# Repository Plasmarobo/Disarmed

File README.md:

# DISARMED!

Heavily inspired by [Keep Talking and Nobody Explodes](https://keeptalkinggame.com/) and [Bomb Corp](https://www.jackboxgames.com/bomb-corp/).

A physical "Bop-It for adults". 

This ammounts to a electroncs and software programming project, with a side-helping of game design and art!

## The SSD Control Panel
The SSD Control panel provides control lines (including manually adjustable brightness) for up to 8 SSD panels with 4 digits each. That is a grand total of 32 digits per board, with 4 brightness zones.
This board is driven by an ATTiny85, which provide an I2C interface to the system at large, and shifts out data to the LED driver chips.
Software will come later.

## The Analog Control Panel
The analog control panel uses DAC and ADC chips to provide analog read and write functions. External I2C interface provided by an ATTiny85. 
The software drivers for this board are still in the works. It will eventually be able to read from analog inputs and write to some interesting analog displays!

## The Switch Control Board
The Switch Control Board uses a number of digital I/O expanders to provide a vast number of pulled-up digital inputs. It has an ATMega328 on board. The Mega chip, with more ports and power, gives us and on-board USB port for programming and diagnostics. The many serial peripherals juggle the master relationship with the expanders and the slave relationship with the external system. Some pins are enabled to drive optional LEDs connected to the switches or mounted on the display.

The software for this is not yet written, but I'm looking forward to the increased power and peripherals vs the ATTiny85.

### The Switch Board
The switch panel contains both analog potentiometers and SPST switches. These will be the primary user input at some point.
Shown is an early prototype of the layout. Eventually more complex and varied inputs will be added. Some of the empty cutouts are for SSD displays not pictured.

The eventual plan is to laser cut and paint and acrylic panel to fit into a case. An alternative may be to 3D print some slotable modules and a motherboard panel to hold them.

## The LED Module
The LED Module drives a series of LED Bar Graph displays, including a few unique circular displays.
The board is essentially a giant shift register that can source proper current to each LED.

Lesson Learned: Double, Triple, Quadruple check your sizing on parts. I eneded up using an ultra-fine pitch SMD resistor array.
I managed to get a few of them down successfully, but ended up bridging the others. My solution was to cut the traces and manually solder THT resistors on the back of the panel.
Fixed in the other designs: used much larger chip resistors.

The board is driven by an onboard ATTiny85, running some custom firmware that includes the TinyWireS library. Unfortunately still interating on the software, but the chip provides and I2C slave that allows a master to write to an output array: buffering the shift register output.
The same set of pins is also used as the ISP interface.

A NodeMCU ESP8266 breakout is being used as a i2c master test.

## The SSD Module
The Seven Segment Display Module is something I unfortunately based on the LD8041C/D series of 20mm seven segment displays.
Having bought several 10 years ago, I found that they seem to be no longer manufactured, so I just have the one board that is finished.
JCLPCB manufactures in minimum lots of 5, so I have 4 useless, large PCBs. At least the one works.

(For the REV2 board, the one I got manufactured, I accidently left out a single line segment of a trace when refactoring some of the runs... thankfully, I was able to bridge the gap with a single wire. This is fixed in REV3+).

In the future, I'll source some new SSD parts and update the boards, possibly with a denser layout.

The board uses MAX7219CNG LED/IO drivers over SPI. A MCP41010 is used to digitally control ISET, though in practice this was set to it's maximum value, and the SSD brightness is controlled via the Intensity register rin the MAX7219.

The test code was prototyped on a NodeMCU ESP8266 breakout, and then ported down to a Adafruit Trinket (ATTiny85). The TinySPI library was used to bridge the gaps.

I tried using libraries for both the MAX7219 and MCP41010 chip, but took exception to the complexity of the code and ended up implementing my own simple driving functions.
Future revisions of the board may implement an I2C interface and use an on-board MCU to drive the MAC7219 and MCP41010.

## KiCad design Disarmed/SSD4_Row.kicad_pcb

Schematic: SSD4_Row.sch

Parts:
D1, D2, D3, D4: HDSP-5500; VDMRX10C0
J1: Conn_02x02_Odd_Even; PinSocket_2x02_P2.54mm_Vertical
J2: Conn_02x04_Odd_Even; PinSocket_2x04_P2.54mm_Vertical

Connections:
/DIG_0: D1.3 (COM), D1.8 (COM), J1.1
/DIG_1: D2.3 (COM), D2.8 (COM), J1.3
/DIG_2: D3.3 (COM), D3.8 (COM), J1.2
/DIG_3: D4.3 (COM), D4.8 (COM), J1.4
/SEG_A: D1.7 (A), D2.7 (A), D3.7 (A), D4.7 (A), J2.7
/SEG_B: D1.6 (B), D2.6 (B), D3.6 (B), D4.6 (B), J2.5
/SEG_C: D1.4 (C), D2.4 (C), D3.4 (C), D4.4 (C), J2.6
/SEG_D: D1.2 (D), D2.2 (D), D3.2 (D), D4.2 (D), J2.4
/SEG_DP: D1.5 (DP), D2.5 (DP), D3.5 (DP), D4.5 (DP), J2.8
/SEG_E: D1.1 (E), D2.1 (E), D3.1 (E), D4.1 (E), J2.2
/SEG_F: D1.9 (F), D2.9 (F), D3.9 (F), D4.9 (F), J2.1
/SEG_G: D1.10 (G), D2.10 (G), D3.10 (G), D4.10 (G), J2.3

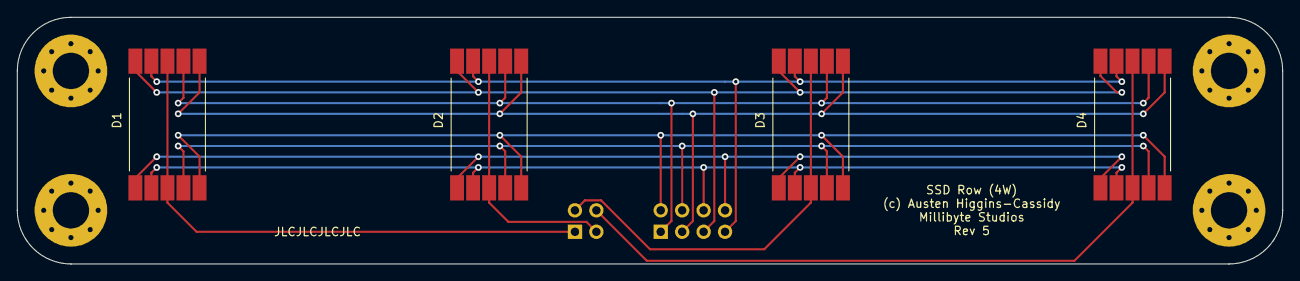
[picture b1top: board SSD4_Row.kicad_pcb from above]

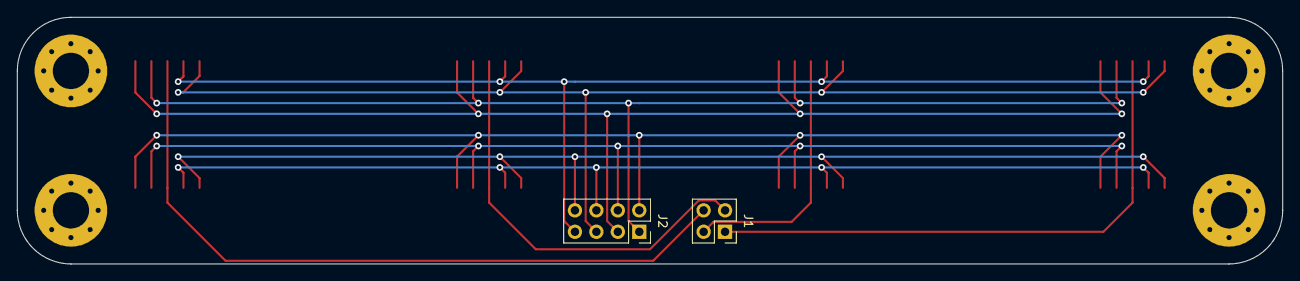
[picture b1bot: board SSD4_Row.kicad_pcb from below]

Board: 2 copper layers, 149.9 x 29.2 mm, 6 parts (2 on the bottom side), 12 nets.

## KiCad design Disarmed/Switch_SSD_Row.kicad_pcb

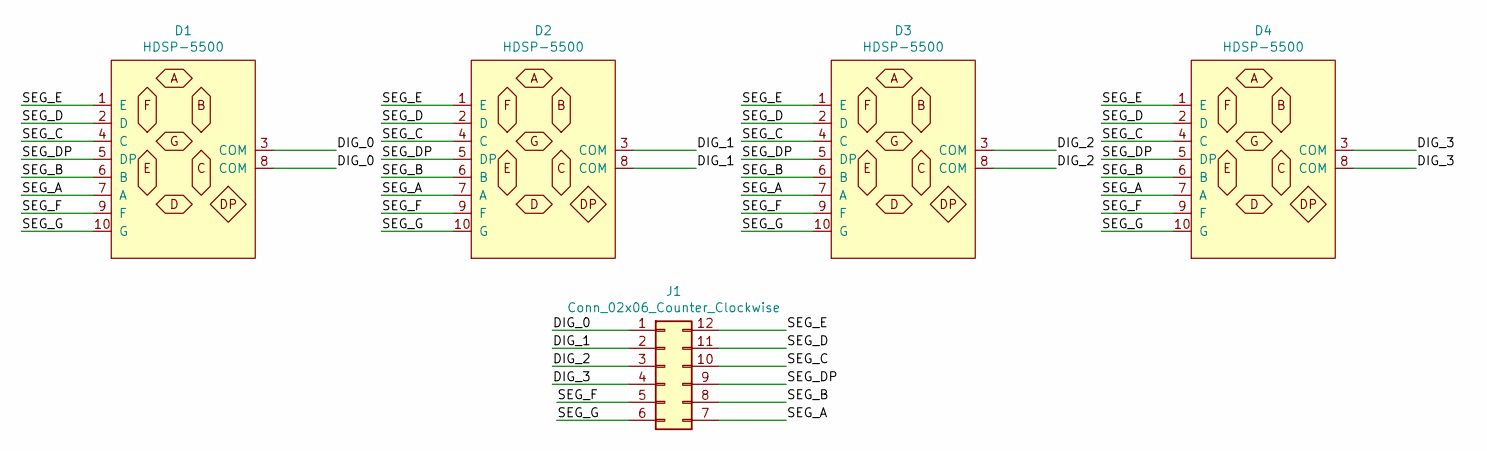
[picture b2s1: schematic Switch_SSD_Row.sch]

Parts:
D1, D2, D3, D4: HDSP-5500
J1: Conn_02x06_Counter_Clockwise; PinSocket_2x06_P2.54mm_Vertical

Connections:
/DIG_0: D1.3 (COM), D1.8 (COM), J1.1
/DIG_1: D2.3 (COM), D2.8 (COM), J1.2
/DIG_2: D3.3 (COM), D3.8 (COM), J1.3
/DIG_3: D4.3 (COM), D4.8 (COM), J1.4
/SEG_A: D1.7 (A), D2.7 (A), D3.7 (A), D4.7 (A), J1.7
/SEG_B: D1.6 (B), D2.6 (B), D3.6 (B), D4.6 (B), J1.8
/SEG_C: D1.4 (C), D2.4 (C), D3.4 (C), D4.4 (C), J1.10
/SEG_D: D1.2 (D), D2.2 (D), D3.2 (D), D4.2 (D), J1.11
/SEG_DP: D1.5 (DP), D2.5 (DP), D3.5 (DP), D4.5 (DP), J1.9
/SEG_E: D1.1 (E), D2.1 (E), D3.1 (E), D4.1 (E), J1.12
/SEG_F: D1.9 (F), D2.9 (F), D3.9 (F), D4.9 (F), J1.5
/SEG_G: D1.10 (G), D2.10 (G), D3.10 (G), D4.10 (G), J1.6

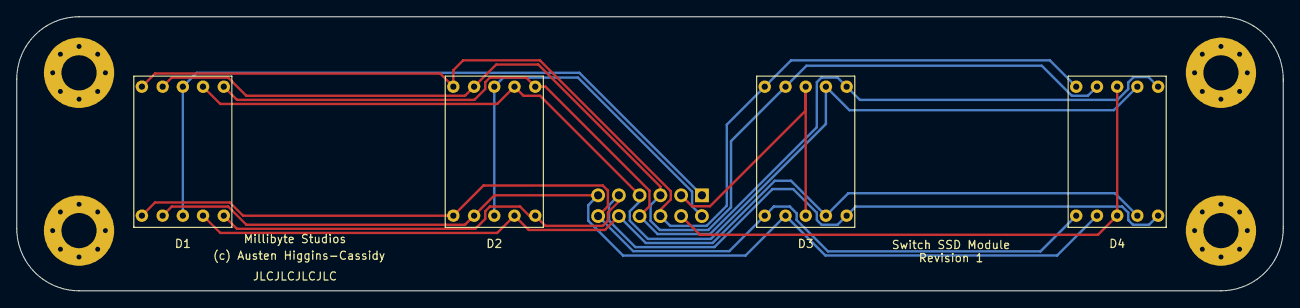
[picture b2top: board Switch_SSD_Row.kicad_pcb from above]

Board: 2 copper layers, 154.9 x 33.5 mm, 5 parts (1 on the bottom side), 12 nets.

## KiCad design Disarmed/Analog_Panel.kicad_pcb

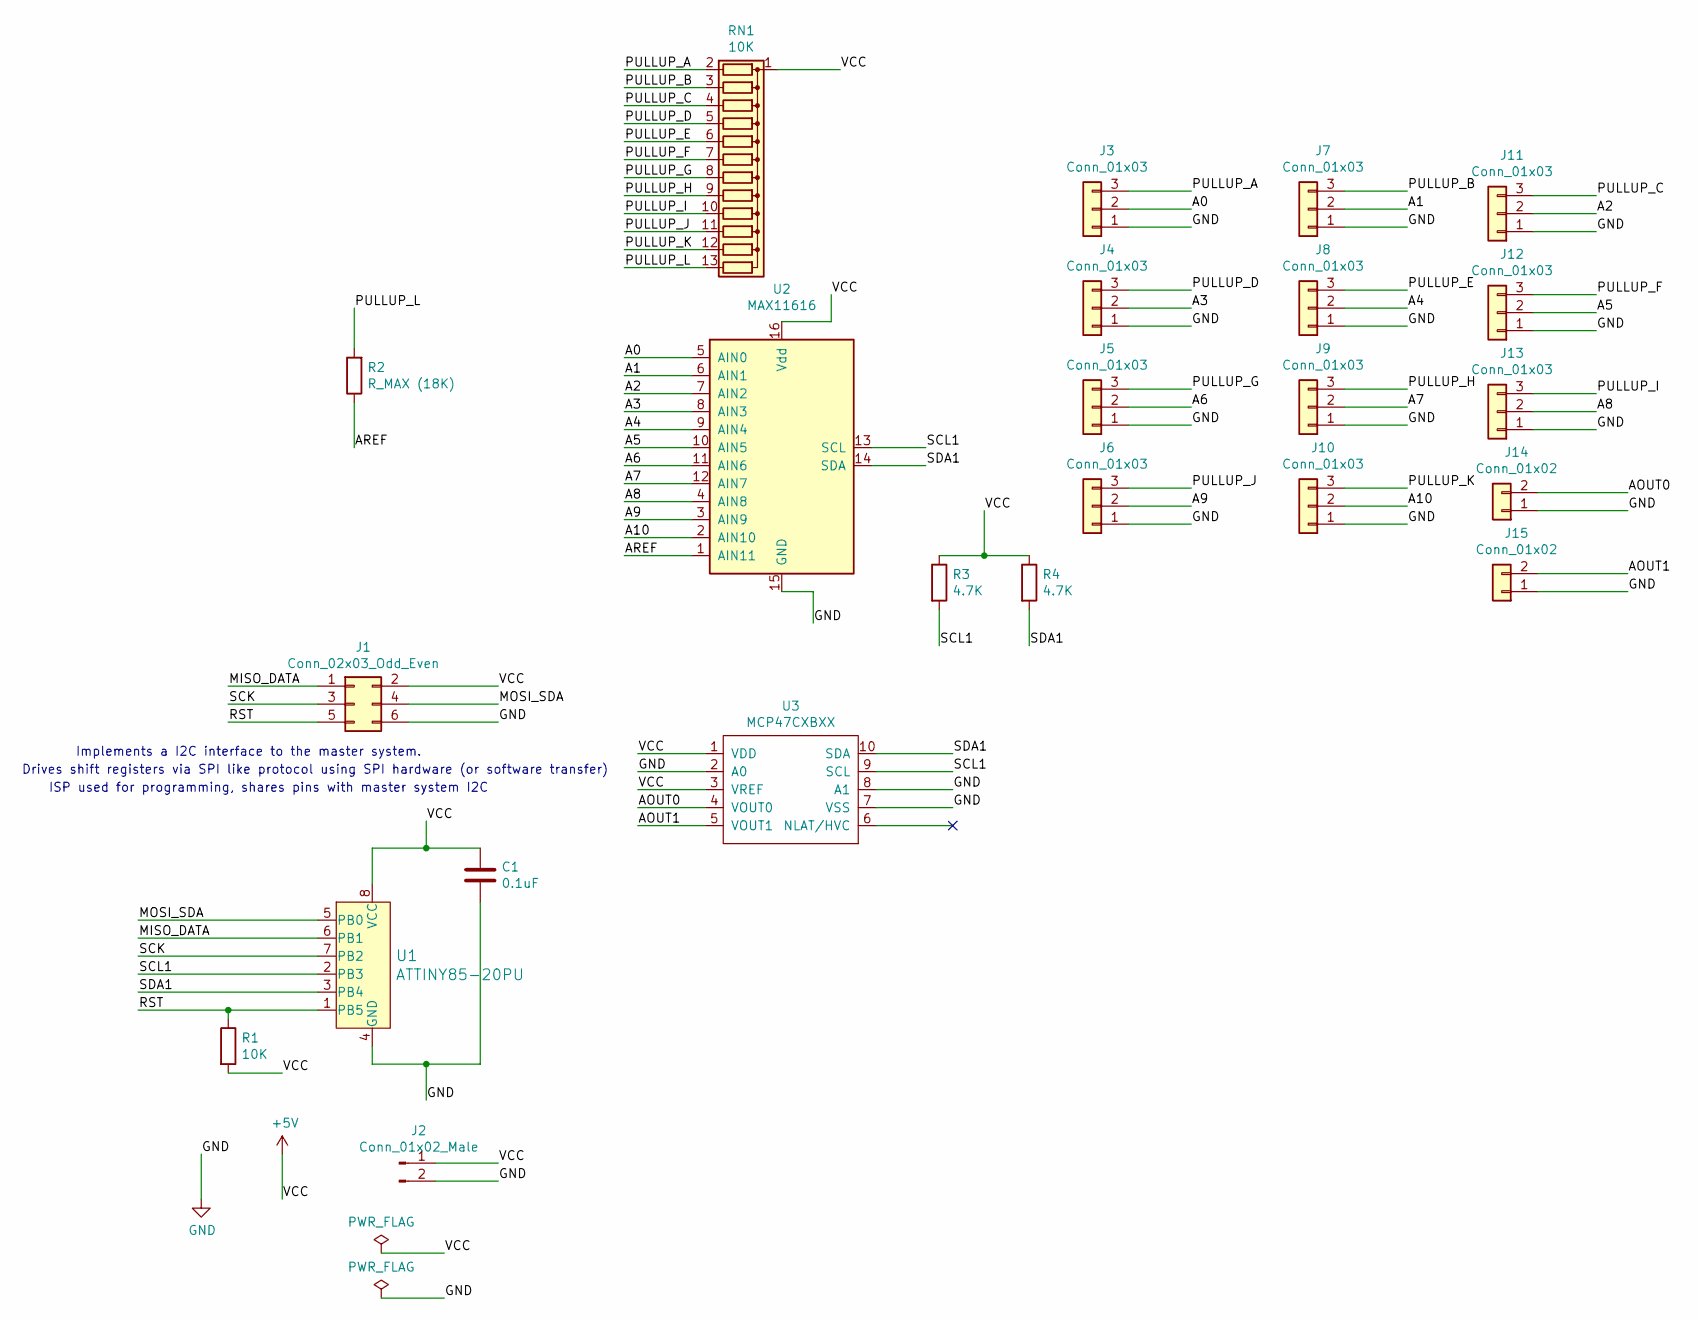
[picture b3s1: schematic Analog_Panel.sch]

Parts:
C1: 0.1uF; C_1812_4532Metric_Pad1.57x3.40mm_HandSolder
J1: Conn_02x03_Odd_Even; PinHeader_2x03_P2.54mm_Vertical
J2: Conn_01x02_Male; PinHeader_1x02_P2.54mm_Vertical
J3, J4, J5, J6, J7, J8, J9, J10, J11, J12, J13: Conn_01x03; PinSocket_1x03_P2.54mm_Vertical
J14, J15: Conn_01x02; PinSocket_1x02_P2.54mm_Vertical
R1: 10K; R_1210_3225Metric_Pad1.30x2.65mm_HandSolder
R2: R_MAX (18K); R_1210_3225Metric_Pad1.30x2.65mm_HandSolder
R3, R4: 4.7K; R_1210_3225Metric_Pad1.30x2.65mm_HandSolder
RN1: 10K; 4814P-2-103LF
U1: ATTINY85-20PU; DIP-8_W7.62mm; MPN ATTINY85-20PU; Digi-Key_PN ATTINY85-20PU-ND
U2: MAX11616; QSOP-16_3.9x4.9mm_P0.635mm
U3: MCP47CXBXX; MSOP-10-1EP_3x3mm_P0.5mm_EP1.68x1.88mm_ThermalVias

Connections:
+5V: C1.1, J1.2, J2.1, R1.2, R3.1, R4.1, RN1.1 (common), U1.8 (VCC), U2.16 (Vdd), U3.1 (VDD), U3.3 (VREF)
/A0: J3.2, U2.5 (AIN0)
/A1: J7.2, U2.6 (AIN1)
/A2: J11.2, U2.7 (AIN2)
/A3: J4.2, U2.8 (AIN3)
/A4: J8.2, U2.9 (AIN4)
/A5: J12.2, U2.10 (AIN5)
/A6: J5.2, U2.11 (AIN6)
/A7: J9.2, U2.12 (AIN7)
/A8: J13.2, U2.4 (AIN8)
/A9: J6.2, U2.3 (AIN9)
/A10: J10.2, U2.2 (AIN10)
/AOUT0: J14.2, U3.4 (VOUT0)
/AOUT1: J15.2, U3.5 (VOUT1)
/AREF: R2.1, U2.1 (AIN11)
/MISO_DATA: J1.1, U1.6 (PB1)
/MOSI_SDA: J1.4, U1.5 (PB0)
/PULLUP_A: J3.3, RN1.2 (R1)
/PULLUP_B: J7.3, RN1.3 (R2)
/PULLUP_C: J11.3, RN1.4 (R3)
/PULLUP_D: J4.3, RN1.5 (R4)
/PULLUP_E: J8.3, RN1.6 (R5)
/PULLUP_F: J12.3, RN1.7 (R6)
/PULLUP_G: J5.3, RN1.8 (R7)
/PULLUP_H: J9.3, RN1.9 (R8)
/PULLUP_I: J13.3, RN1.10 (R9)
/PULLUP_J: J6.3, RN1.11 (R10)
/PULLUP_K: J10.3, RN1.12 (R11)
/PULLUP_L: R2.2, RN1.13 (R12)
/RST: J1.5, R1.1, U1.1 (PB5)
/SCK: J1.3, U1.7 (PB2)
/SCL1: R3.2, U1.2 (PB3), U2.13 (SCL), U3.9 (SCL)
/SDA1: R4.2, U1.3 (PB4), U2.14 (SDA), U3.10 (SDA)
GND: C1.2, J1.6, J2.2, J3.1, J4.1, J5.1, J6.1, J7.1, J8.1, J9.1, J10.1, J11.1, J12.1, J13.1, J14.1, J15.1, U1.4 (GND), U2.15 (GND), U3.2 (A0), U3.7 (VSS), U3.8 (A1)

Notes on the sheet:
Implements a I2C interface to the master system.
Drives shift registers via SPI like protocol using SPI hardware (or software transfer)
ISP used for programming, shares pins with master system I2C

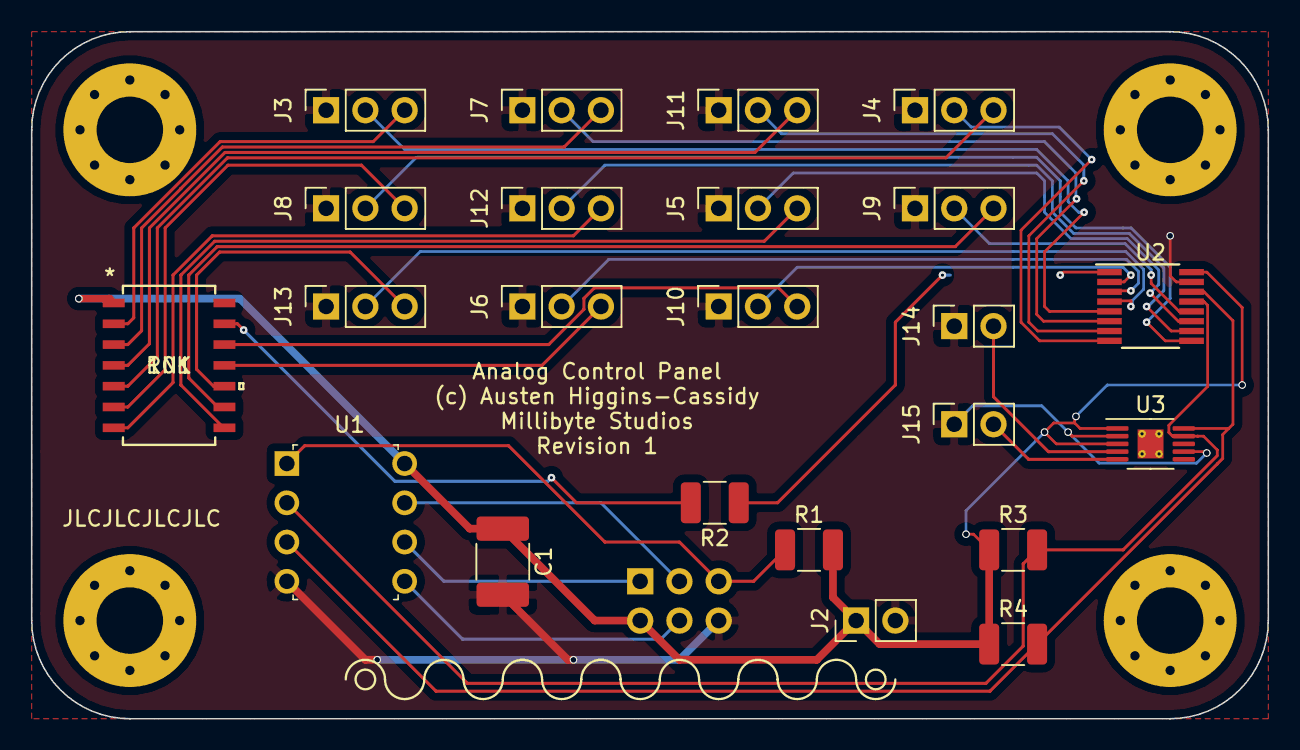
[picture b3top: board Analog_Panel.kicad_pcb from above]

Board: 2 copper layers, 80.0 x 44.5 mm, 24 parts (1 on the bottom side), 34 nets.

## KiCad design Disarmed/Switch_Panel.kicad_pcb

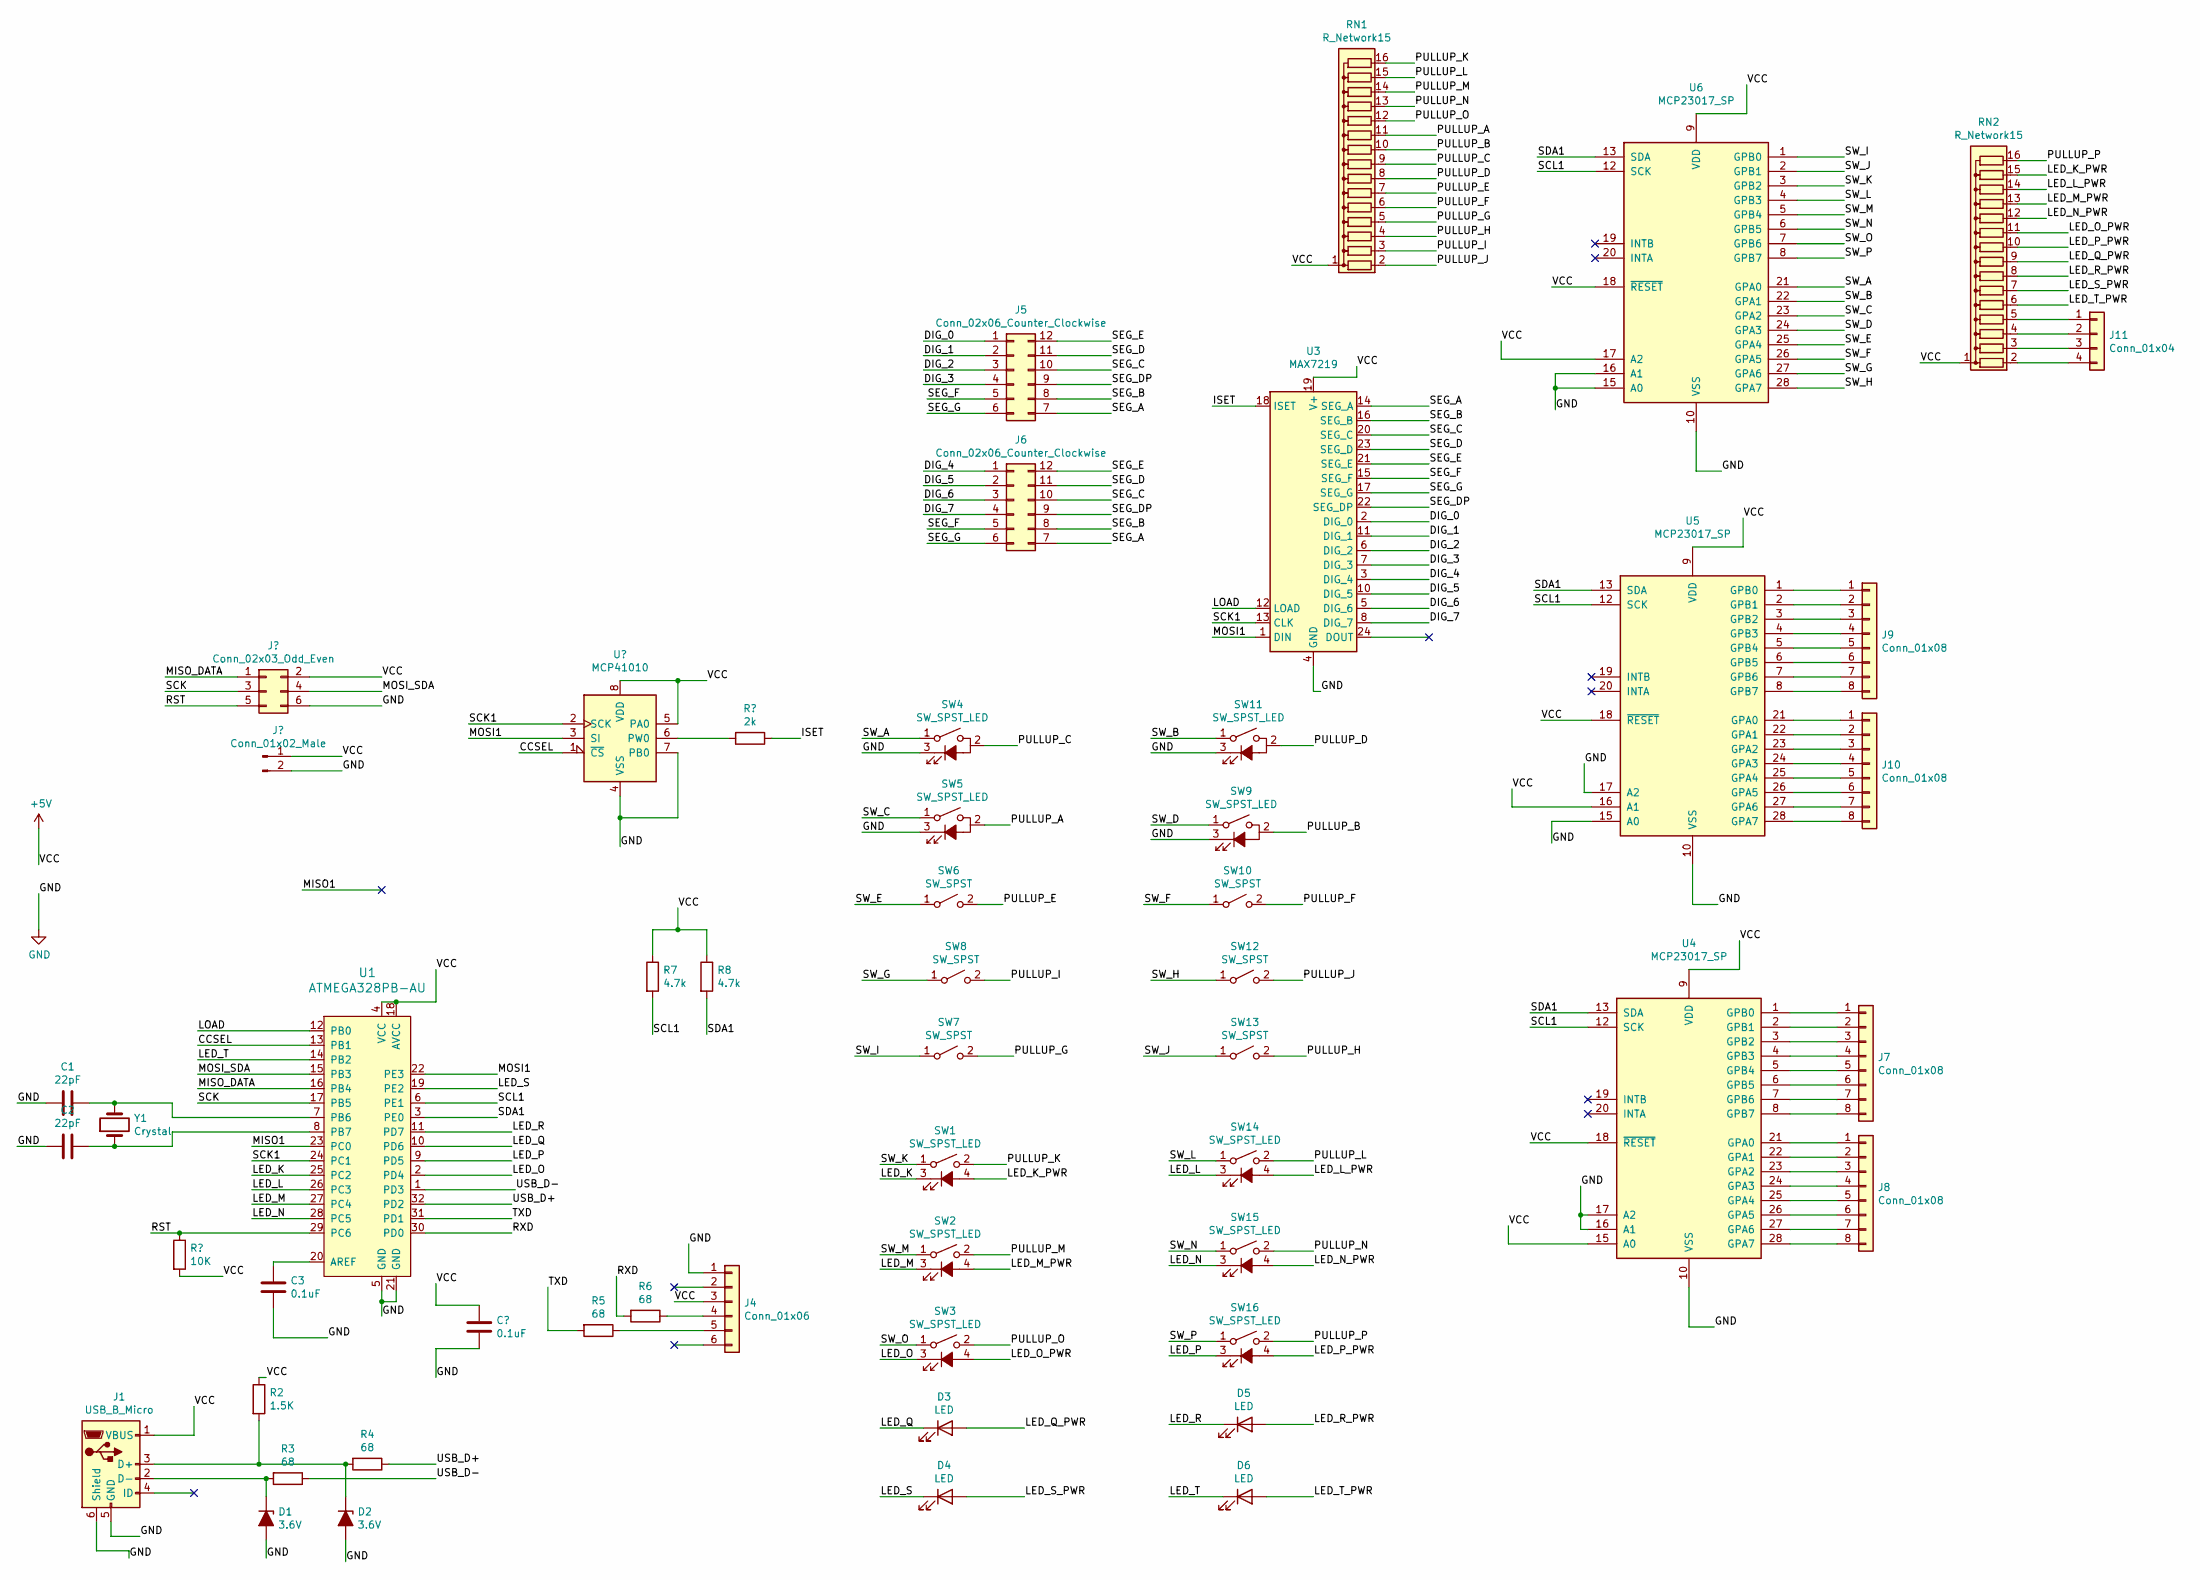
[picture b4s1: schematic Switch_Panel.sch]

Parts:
C1, C2: 22pF; C_1812_4532Metric_Pad1.57x3.40mm_HandSolder
C3, C4: 0.1uF; C_1812_4532Metric_Pad1.57x3.40mm_HandSolder
D1, D2: 3.6V; D_DO-35_SOD27_P7.62mm_Horizontal
D3, D4, D5, D6: LED; LED_D3.0mm
J1: USB_B_Micro; USB_Micro_B_Female_10118194-0001LF
J2: Conn_01x02_Male; PinHeader_1x02_P2.54mm_Vertical
J3: Conn_02x03_Odd_Even; PinHeader_2x03_P2.54mm_Vertical
J4: Conn_01x06; PinSocket_1x06_P2.54mm_Vertical
J5, J6: Conn_02x06_Counter_Clockwise; PinSocket_2x06_P2.54mm_Vertical
J7, J8, J9, J10: Conn_01x08; PinSocket_1x08_P2.54mm_Vertical
J11: Conn_01x04; PinSocket_1x04_P2.54mm_Vertical
R1: 10K; R_1210_3225Metric_Pad1.30x2.65mm_HandSolder
R2: 1.5K; R_1210_3225Metric_Pad1.30x2.65mm_HandSolder
R3, R4: 68; R_1812_4532Metric_Pad1.30x3.40mm_HandSolder
R5, R6: 68; R_1210_3225Metric_Pad1.30x2.65mm_HandSolder
R7, R8: 4.7k; R_1210_3225Metric_Pad1.30x2.65mm_HandSolder
R9: 2k; R_1210_3225Metric_Pad1.30x2.65mm_HandSolder
RN1, RN2: R_Network15; SOIC-16_W7.5mm
SW1, SW2, SW3, SW14, SW15, SW16: SW_SPST_LED; PinSocket_2x02_P2.54mm_Vertical
SW4, SW5, SW9, SW11: SW_SPST_LED; PinSocket_1x03_P2.54mm_Vertical
SW6, SW7, SW8, SW10, SW12, SW13: SW_SPST; PinSocket_1x02_P2.54mm_Vertical
U1: ATMEGA328PB-AU; TQFP-32_7x7mm; MPN ATMEGA328PB-AU; Digi-Key_PN ATMEGA328PB-AU-ND
U2: MCP41010; DIP-8_W7.62mm
U3: MAX7219; DIP-24_W7.62mm
U4, U5, U6: MCP23017_SP; DIP-28_W7.62mm
Y1: Crystal; Crystal_HC49-U_Vertical

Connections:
+5V: C4.1, J1.1 (VBUS), J2.1, J3.2, J4.3, R1.2, R2.1, R7.1, R8.1, RN1.1 (common), RN2.1 (common), U1.4 (VCC), U1.18 (AVCC), U2.5 (PA0), U2.8 (VDD), U3.19 (V+), U4.9 (VDD), U4.15 (A0), U4.18 (~RESET~), U5.9 (VDD), U5.16 (A1), U5.18 (~RESET~), U6.9 (VDD), U6.17 (A2), U6.18 (~RESET~)
/CCSEL: U1.13 (PB1), U2.1 (~CS)
/DIG_0: J5.1, U3.2 (DIG_0)
/DIG_1: J5.2, U3.11 (DIG_1)
/DIG_2: J5.3, U3.6 (DIG_2)
/DIG_3: J5.4, U3.7 (DIG_3)
/DIG_4: J6.1, U3.3 (DIG_4)
/DIG_5: J6.2, U3.10 (DIG_5)
/DIG_6: J6.3, U3.5 (DIG_6)
/DIG_7: J6.4, U3.8 (DIG_7)
/ISET: R9.1, U3.18 (ISET)
/LED_K: SW1.3 (K), U1.25 (PC2)
/LED_K_PWR: RN2.15 (R14), SW1.4 (A)
/LED_L: SW14.3 (K), U1.26 (PC3)
/LED_L_PWR: RN2.14 (R13), SW14.4 (A)
/LED_M: SW2.3 (K), U1.27 (PC4)
/LED_M_PWR: RN2.13 (R12), SW2.4 (A)
/LED_N: SW15.3 (K), U1.28 (PC5)
/LED_N_PWR: RN2.12 (R11), SW15.4 (A)
/LED_O: SW3.3 (K), U1.2 (PD4)
/LED_O_PWR: RN2.11 (R10), SW3.4 (A)
/LED_P: SW16.3 (K), U1.9 (PD5)
/LED_P_PWR: RN2.10 (R9), SW16.4 (A)
/LED_Q: D3.1 (K), U1.10 (PD6)
/LED_Q_PWR: D3.2 (A), RN2.9 (R8)
/LED_R: D5.1 (K), U1.11 (PD7)
/LED_R_PWR: D5.2 (A), RN2.8 (R7)
/LED_S: D4.1 (K), U1.19 (PE2)
/LED_S_PWR: D4.2 (A), RN2.7 (R6)
/LED_T: D6.1 (K), U1.14 (PB2)
/LED_T_PWR: D6.2 (A), RN2.6 (R5)
/LOAD: U1.12 (PB0), U3.12 (LOAD)
/MISO_DATA: J3.1, U1.16 (PB4)
/MOSI1: U1.22 (PE3), U2.3 (SI), U3.1 (DIN)
/MOSI_SDA: J3.4, U1.15 (PB3)
/PULLUP_A: RN1.11 (R10), SW5.2 (Headlamp)
/PULLUP_B: RN1.10 (R9), SW9.2 (Headlamp)
/PULLUP_C: RN1.9 (R8), SW4.2 (Headlamp)
/PULLUP_D: RN1.8 (R7), SW11.2 (Headlamp)
/PULLUP_E: RN1.7 (R6), SW6.2 (B)
/PULLUP_F: RN1.6 (R5), SW10.2 (B)
/PULLUP_G: RN1.5 (R4), SW7.2 (B)
/PULLUP_H: RN1.4 (R3), SW13.2 (B)
/PULLUP_I: RN1.3 (R2), SW8.2 (B)
/PULLUP_J: RN1.2 (R1), SW12.2 (B)
/PULLUP_K: RN1.16 (R15), SW1.2
/PULLUP_L: RN1.15 (R14), SW14.2
/PULLUP_M: RN1.14 (R13), SW2.2
/PULLUP_N: RN1.13 (R12), SW15.2
/PULLUP_O: RN1.12 (R11), SW3.2
/PULLUP_P: RN2.16 (R15), SW16.2
/RST: J3.5, R1.1, U1.29 (PC6)
/RXD: R6.2, U1.30 (PD0)
/SCK: J3.3, U1.17 (PB5)
/SCK1: U1.24 (PC1), U2.2 (SCK), U3.13 (CLK)
/SCL1: R7.2, U1.6 (PE1), U4.12 (SCK), U5.12 (SCK), U6.12 (SCK)
/SDA1: R8.2, U1.3 (PE0), U4.13 (SDA), U5.13 (SDA), U6.13 (SDA)
/SEG_A: J5.7, J6.7, U3.14 (SEG_A)
/SEG_B: J5.8, J6.8, U3.16 (SEG_B)
/SEG_C: J5.10, J6.10, U3.20 (SEG_C)
/SEG_D: J5.11, J6.11, U3.23 (SEG_D)
/SEG_DP: J5.9, J6.9, U3.22 (SEG_DP)
/SEG_E: J5.12, J6.12, U3.21 (SEG_E)
/SEG_F: J5.5, J6.5, U3.15 (SEG_F)
/SEG_G: J5.6, J6.6, U3.17 (SEG_G)
/SW_A: SW4.1, U6.21 (GPA0)
/SW_B: SW11.1, U6.22 (GPA1)
/SW_C: SW5.1, U6.23 (GPA2)
/SW_D: SW9.1, U6.24 (GPA3)
/SW_E: SW6.1 (A), U6.25 (GPA4)
/SW_F: SW10.1 (A), U6.26 (GPA5)
/SW_G: SW8.1 (A), U6.27 (GPA6)
/SW_H: SW12.1 (A), U6.28 (GPA7)
/SW_I: SW7.1 (A), U6.1 (GPB0)
/SW_J: SW13.1 (A), U6.2 (GPB1)
/SW_K: SW1.1, U6.3 (GPB2)
/SW_L: SW14.1, U6.4 (GPB3)
/SW_M: SW2.1, U6.5 (GPB4)
/SW_N: SW15.1, U6.6 (GPB5)
/SW_O: SW3.1, U6.7 (GPB6)
/SW_P: SW16.1, U6.8 (GPB7)
/TXD: R5.2, U1.31 (PD1)
/USB_D+: R4.1, U1.32 (PD2)
/USB_D-: R3.1, U1.1 (PD3)
GND: C1.2, C2.2, C3.2, C4.2, D1.2 (A), D2.2 (A), J1.5 (GND), J1.6 (Shield), J2.2, J3.6, J4.1, SW4.3 (K), SW5.3 (K), SW9.3 (K), SW11.3 (K), U1.5 (GND), U1.21 (GND), U2.4 (VSS), U2.7 (PB0), U3.4 (GND), U3.9 (GND), U4.10 (VSS), U4.16 (A1), U4.17 (A2), U5.10 (VSS), U5.15 (A0), U5.17 (A2), U6.10 (VSS), U6.15 (A0), U6.16 (A1)
unnamed: C1.1, U1.7 (PB6), Y1.2
unnamed: C2.1, U1.8 (PB7), Y1.1
unnamed: C3.1, U1.20 (AREF)
unnamed: D1.1 (K), J1.2 (D-), R3.2
unnamed: D2.1 (K), J1.3 (D+), R2.2, R4.2
unnamed: J4.4, R6.1
unnamed: J4.5, R5.1
unnamed: J7.1, U4.1 (GPB0)
unnamed: J7.2, U4.2 (GPB1)
unnamed: J7.3, U4.3 (GPB2)
unnamed: J7.4, U4.4 (GPB3)
unnamed: J7.5, U4.5 (GPB4)
unnamed: J7.6, U4.6 (GPB5)
unnamed: J7.7, U4.7 (GPB6)
unnamed: J7.8, U4.8 (GPB7)
unnamed: J8.1, U4.21 (GPA0)
unnamed: J8.2, U4.22 (GPA1)
unnamed: J8.3, U4.23 (GPA2)
unnamed: J8.4, U4.24 (GPA3)
unnamed: J8.5, U4.25 (GPA4)
unnamed: J8.6, U4.26 (GPA5)
unnamed: J8.7, U4.27 (GPA6)
unnamed: J8.8, U4.28 (GPA7)
unnamed: J9.1, U5.1 (GPB0)
unnamed: J9.2, U5.2 (GPB1)
unnamed: J9.3, U5.3 (GPB2)
unnamed: J9.4, U5.4 (GPB3)
unnamed: J9.5, U5.5 (GPB4)
unnamed: J9.6, U5.6 (GPB5)
unnamed: J9.7, U5.7 (GPB6)
unnamed: J9.8, U5.8 (GPB7)
unnamed: J10.1, U5.21 (GPA0)
unnamed: J10.2, U5.22 (GPA1)
unnamed: J10.3, U5.23 (GPA2)
unnamed: J10.4, U5.24 (GPA3)
unnamed: J10.5, U5.25 (GPA4)
unnamed: J10.6, U5.26 (GPA5)
unnamed: J10.7, U5.27 (GPA6)
unnamed: J10.8, U5.28 (GPA7)
unnamed: J11.1, RN2.5 (R4)
unnamed: J11.2, RN2.4 (R3)
unnamed: J11.3, RN2.3 (R2)
unnamed: J11.4, RN2.2 (R1)
unnamed: R9.2, U2.6 (PW0)

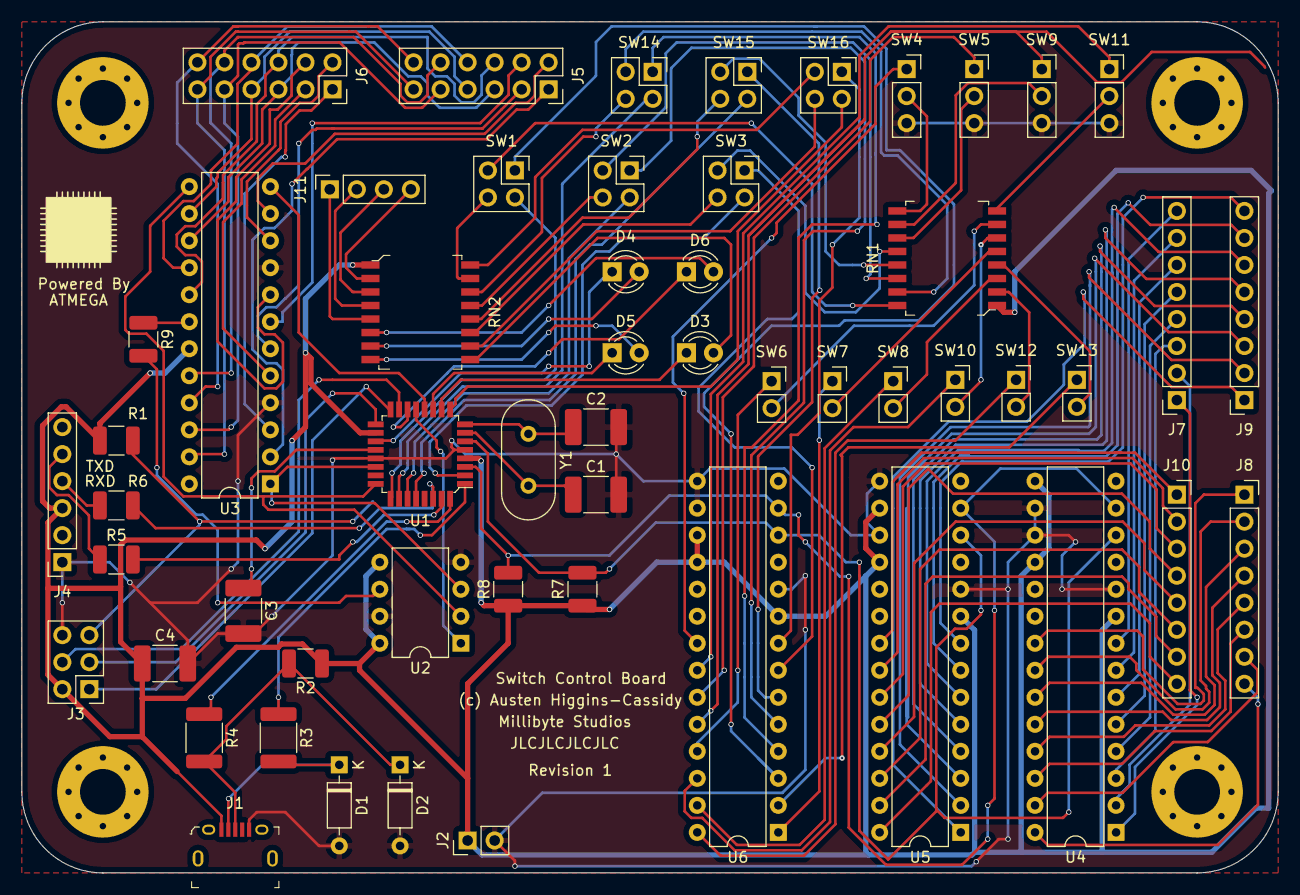
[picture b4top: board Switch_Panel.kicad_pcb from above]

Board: 2 copper layers, 118.1 x 80.0 mm, 55 parts (0 on the bottom side), 129 nets.

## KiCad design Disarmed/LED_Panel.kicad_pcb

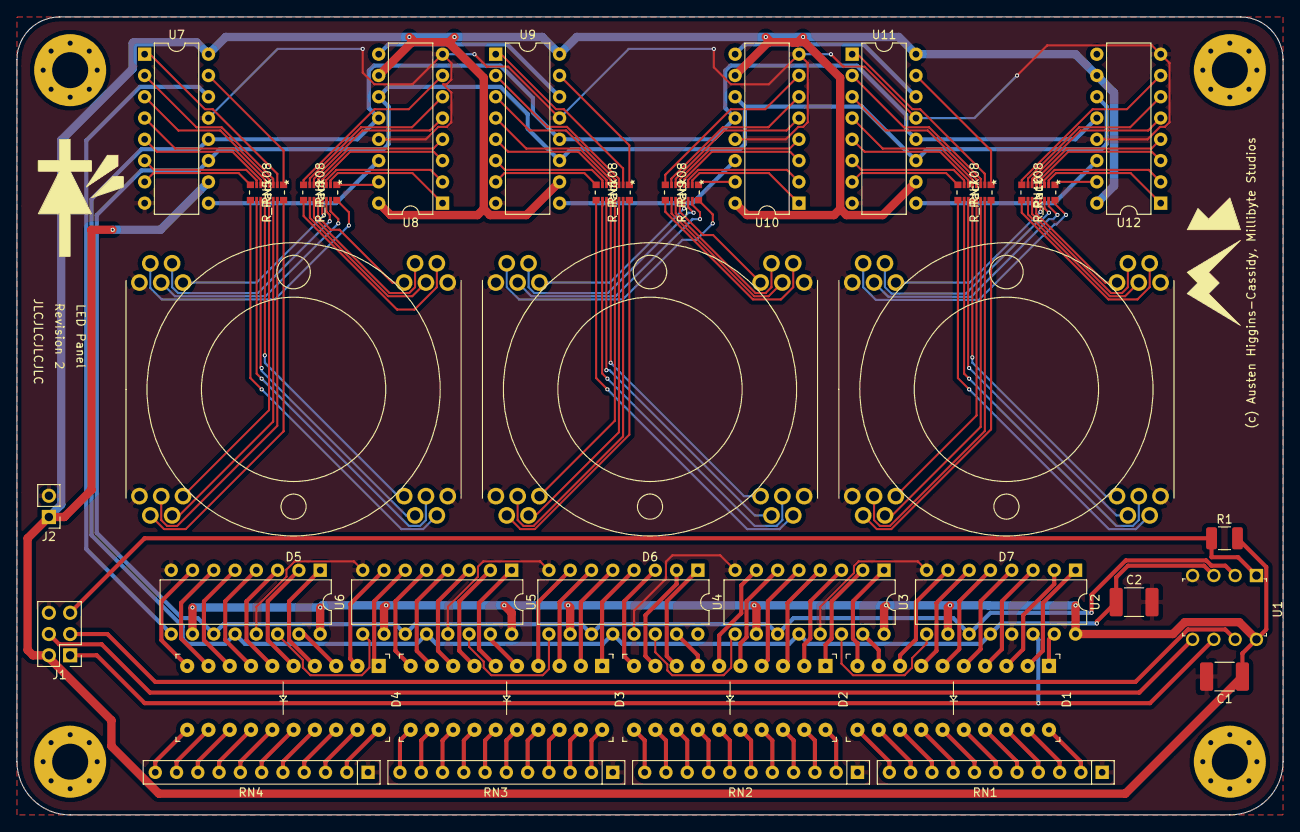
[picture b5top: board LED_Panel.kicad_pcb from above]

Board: 2 copper layers, 151.1 x 95.3 mm, 34 parts (0 on the bottom side), 194 nets.

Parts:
C1: 0.1uF; C_1812_4532Metric_Pad1.57x3.40mm_HandSolder
C2: 10uF; C_1812_4532Metric_Pad1.57x3.40mm_HandSolder
D1, D2: LTA-1000G; LED_Bar_Graph_LTA-1000
D3: LTA-1000Y; LED_Bar_Graph_LTA-1000
D4: LTA-1000HR; LED_Bar_Graph_LTA-1000
D5, D6, D7: LED-CCL-A-A-XXXX-6H; LED-CCL-A-A-XXXX-H6
J1: Conn_02x03_Odd_Even; PinHeader_2x03_P2.54mm_Vertical
J2: Conn_01x02_Male; PinHeader_1x02_P2.54mm_Vertical
R1: 10K; R_1210_3225Metric_Pad1.30x2.65mm_HandSolder
RN1, RN2, RN3, RN4: 4.7K; R_Array_SIP11
RN5, RN6, RN7, RN8, RN9, RN10: R_Pack08; EXB-2HV471JV
U1: ATTINY85-20PU; DIP-8_W7.62mm
U2, U3, U4, U5, U6, U7, U8, U9, U10, U11, U12: 74HC595; DIP-16_W7.62mm

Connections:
+5V: C1.1, J1.2, J2.1, R1.2, U1.8, U2.10, U2.16, U3.10, U3.16, U4.10, U4.16, U5.10, U5.16, U6.10, U6.16, U7.10, U7.16, U8.10, U8.16, U9.10, U9.16, U10.10, U10.16, U11.10, U11.16, U12.10, U12.16
/CLK: U1.2, U2.11, U3.11, U4.11, U5.11, U6.11, U7.11, U8.11, U9.11, U10.11, U11.11, U12.11
/DATA_0: U6.9, U7.14
/DATA_1: U7.9, U8.14
/DATA_2: U8.9, U9.14
/DATA_3: U9.9, U10.14
/DATA_4: U10.9, U11.14
/DATA_5: U11.9, U12.14
/LATCH: C2.1, U1.3, U2.12, U3.12, U4.12, U5.12, U6.12, U7.12, U8.12, U9.12, U10.12, U11.12, U12.12
/MISO_DATA: J1.1, U1.6, U2.14
/MOSI_SDA: J1.4, U1.5
/RST: J1.5, R1.1, U1.1
/SCK: J1.3, U1.7
GND: C1.2, C2.2, D5.5, D5.6, D5.15, D5.16, D6.5, D6.6, D6.15, D6.16, D7.5, D7.6, D7.15, D7.16, J1.6, J2.2, RN1.1, RN2.1, RN3.1, RN4.1, U1.4, U2.8, U2.13, U3.8, U3.13, U4.8, U4.13, U5.8, U5.13, U6.8, U6.13, U7.8, U7.13, U8.8, U8.13, U9.8, U9.13, U10.8, U10.13, U11.8, U11.13, U12.8, U12.13
unnamed: D1.1, U2.15
unnamed: D1.2, U2.1
unnamed: D1.3, U2.2
unnamed: D1.4, U2.3
unnamed: D1.5, U2.4
unnamed: D1.6, U2.5
unnamed: D1.7, U2.6
unnamed: D1.8, U2.7
unnamed: D1.9, U3.15
unnamed: D1.10, U3.1
unnamed: D1.11, RN1.11
unnamed: D1.12, RN1.10
unnamed: D1.13, RN1.9
unnamed: D1.14, RN1.8
unnamed: D1.15, RN1.7
unnamed: D1.16, RN1.6
unnamed: D1.17, RN1.5
unnamed: D1.18, RN1.4
unnamed: D1.19, RN1.3
unnamed: D1.20, RN1.2
unnamed: D2.1, U3.2
unnamed: D2.2, U3.3
unnamed: D2.3, U3.4
unnamed: D2.4, U3.5
unnamed: D2.5, U3.6
unnamed: D2.6, U3.7
unnamed: D2.7, U4.15
unnamed: D2.8, U4.1
unnamed: D2.9, U4.2
unnamed: D2.10, U4.3
unnamed: D2.11, RN2.11
unnamed: D2.12, RN2.10
unnamed: D2.13, RN2.9
unnamed: D2.14, RN2.8
unnamed: D2.15, RN2.7
unnamed: D2.16, RN2.6
unnamed: D2.17, RN2.5
unnamed: D2.18, RN2.4
unnamed: D2.19, RN2.3
unnamed: D2.20, RN2.2
unnamed: D3.1, U4.4
unnamed: D3.2, U4.5
unnamed: D3.3, U4.6
unnamed: D3.4, U4.7
unnamed: D3.5, U5.15
unnamed: D3.6, U5.1
unnamed: D3.7, U5.2
unnamed: D3.8, U5.3
unnamed: D3.9, U5.4
unnamed: D3.10, U5.5
unnamed: D3.11, RN3.11
unnamed: D3.12, RN3.10
unnamed: D3.13, RN3.9
unnamed: D3.14, RN3.8
unnamed: D3.15, RN3.7
unnamed: D3.16, RN3.6
unnamed: D3.17, RN3.5
unnamed: D3.18, RN3.4
unnamed: D3.19, RN3.3
unnamed: D3.20, RN3.2
unnamed: D4.1, U5.6
unnamed: D4.2, U5.7
unnamed: D4.3, U6.15
unnamed: D4.4, U6.1
unnamed: D4.5, U6.2
unnamed: D4.6, U6.3
unnamed: D4.7, U6.4
unnamed: D4.8, U6.5
unnamed: D4.9, U6.6
unnamed: D4.10, U6.7
unnamed: D4.11, RN4.11
unnamed: D4.12, RN4.10
unnamed: D4.13, RN4.9
unnamed: D4.14, RN4.8
unnamed: D4.15, RN4.7
unnamed: D4.16, RN4.6
unnamed: D4.17, RN4.5
unnamed: D4.18, RN4.4
unnamed: D4.19, RN4.3
unnamed: D4.20, RN4.2
unnamed: D5.1, RN8.12
unnamed: D5.2, RN8.11
unnamed: D5.3, RN8.10
unnamed: D5.4, RN8.9
unnamed: D5.7, RN5.9
unnamed: D5.8, RN5.10
unnamed: D5.9, RN5.11
unnamed: D5.10, RN5.12
unnamed: D5.11, RN5.13
unnamed: D5.12, RN5.14
unnamed: D5.13, RN5.15
unnamed: D5.14, RN5.16
unnamed: D5.17, RN8.16
unnamed: D5.18, RN8.15
unnamed: D5.19, RN8.14
unnamed: D5.20, RN8.13
unnamed: D6.1, RN9.12
unnamed: D6.2, RN9.11
unnamed: D6.3, RN9.10
unnamed: D6.4, RN9.9
unnamed: D6.7, RN6.9
unnamed: D6.8, RN6.10
unnamed: D6.9, RN6.11
unnamed: D6.10, RN6.12
unnamed: D6.11, RN6.13
unnamed: D6.12, RN6.14
unnamed: D6.13, RN6.15
unnamed: D6.14, RN6.16
unnamed: D6.17, RN9.16
unnamed: D6.18, RN9.15
unnamed: D6.19, RN9.14
unnamed: D6.20, RN9.13
unnamed: D7.1, RN10.12
unnamed: D7.2, RN10.11
unnamed: D7.3, RN10.10
unnamed: D7.4, RN10.9
unnamed: D7.7, RN7.9
unnamed: D7.8, RN7.10
unnamed: D7.9, RN7.11
unnamed: D7.10, RN7.12
unnamed: D7.11, RN7.13
unnamed: D7.12, RN7.14
unnamed: D7.13, RN7.15
unnamed: D7.14, RN7.16
unnamed: D7.17, RN10.16
unnamed: D7.18, RN10.15
unnamed: D7.19, RN10.14
unnamed: D7.20, RN10.13
unnamed: RN5.1, U7.15
unnamed: RN5.2, U7.1
unnamed: RN5.3, U7.2
unnamed: RN5.4, U7.3
unnamed: RN5.5, U7.4
unnamed: RN5.6, U7.5
unnamed: RN5.7, U7.6
unnamed: RN5.8, U7.7
unnamed: RN6.1, U9.15
unnamed: RN6.2, U9.1
unnamed: RN6.3, U9.2
unnamed: RN6.4, U9.3
unnamed: RN6.5, U9.4
unnamed: RN6.6, U9.5
unnamed: RN6.7, U9.6
unnamed: RN6.8, U9.7
unnamed: RN7.1, U11.15
unnamed: RN7.2, U11.1
unnamed: RN7.3, U11.2
unnamed: RN7.4, U11.3
unnamed: RN7.5, U11.4
unnamed: RN7.6, U11.5
unnamed: RN7.7, U11.6
unnamed: RN7.8, U11.7
unnamed: RN8.1, U8.15
unnamed: RN8.2, U8.1
unnamed: RN8.3, U8.2
unnamed: RN8.4, U8.3
unnamed: RN8.5, U8.4
unnamed: RN8.6, U8.5
unnamed: RN8.7, U8.6
unnamed: RN8.8, U8.7
unnamed: RN9.1, U10.15
unnamed: RN9.2, U10.1
unnamed: RN9.3, U10.2
unnamed: RN9.4, U10.3
unnamed: RN9.5, U10.4
unnamed: RN9.6, U10.5
unnamed: RN9.7, U10.6
unnamed: RN9.8, U10.7
unnamed: RN10.1, U12.15
unnamed: RN10.2, U12.1
unnamed: RN10.3, U12.2
unnamed: RN10.4, U12.3
unnamed: RN10.5, U12.4
unnamed: RN10.6, U12.5
unnamed: RN10.7, U12.6
unnamed: RN10.8, U12.7
unnamed: U2.9, U3.14
unnamed: U3.9, U4.14
unnamed: U4.9, U5.14
unnamed: U5.9, U6.14

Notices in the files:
parts and their libraries:
Copyright 2016 Accelerated Designs. All rights reserved.
